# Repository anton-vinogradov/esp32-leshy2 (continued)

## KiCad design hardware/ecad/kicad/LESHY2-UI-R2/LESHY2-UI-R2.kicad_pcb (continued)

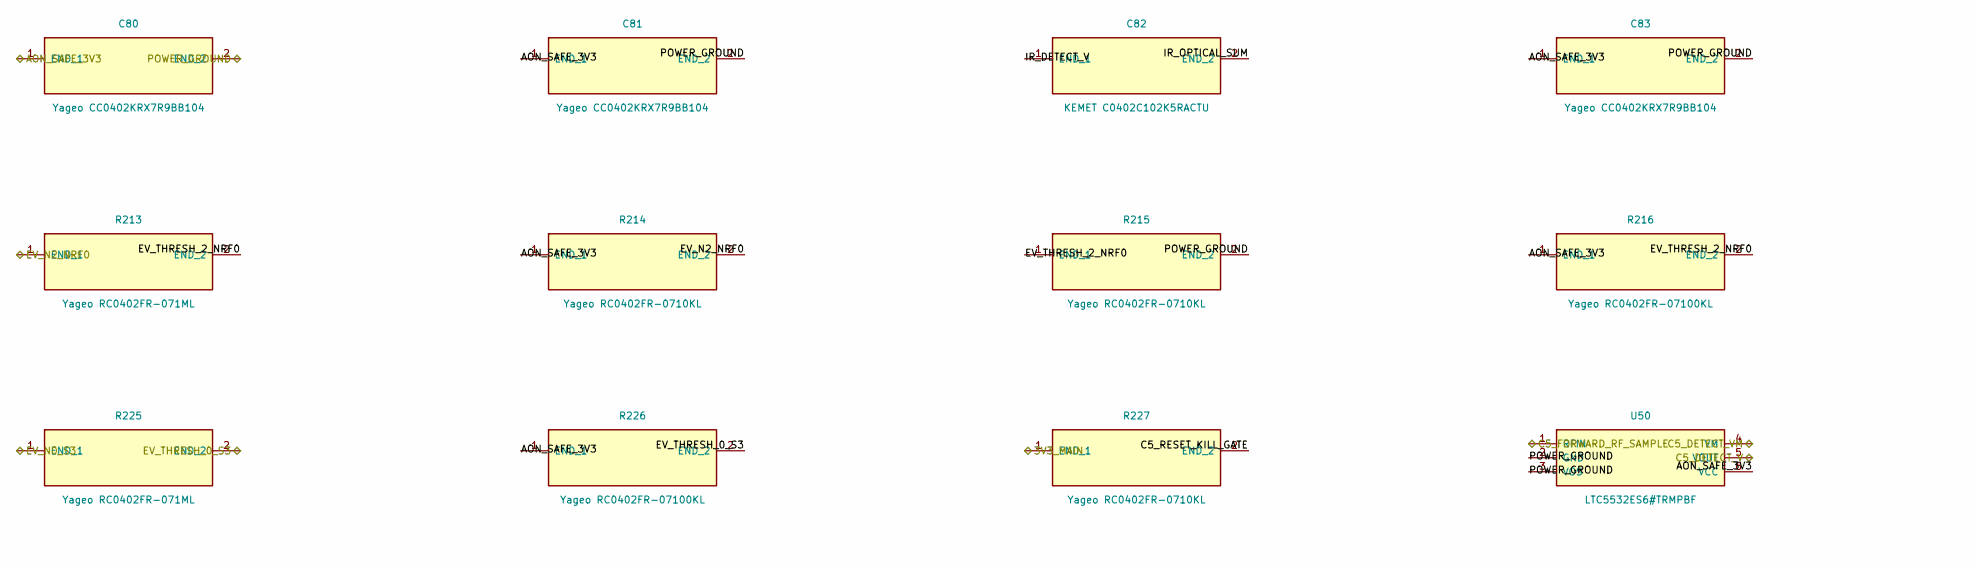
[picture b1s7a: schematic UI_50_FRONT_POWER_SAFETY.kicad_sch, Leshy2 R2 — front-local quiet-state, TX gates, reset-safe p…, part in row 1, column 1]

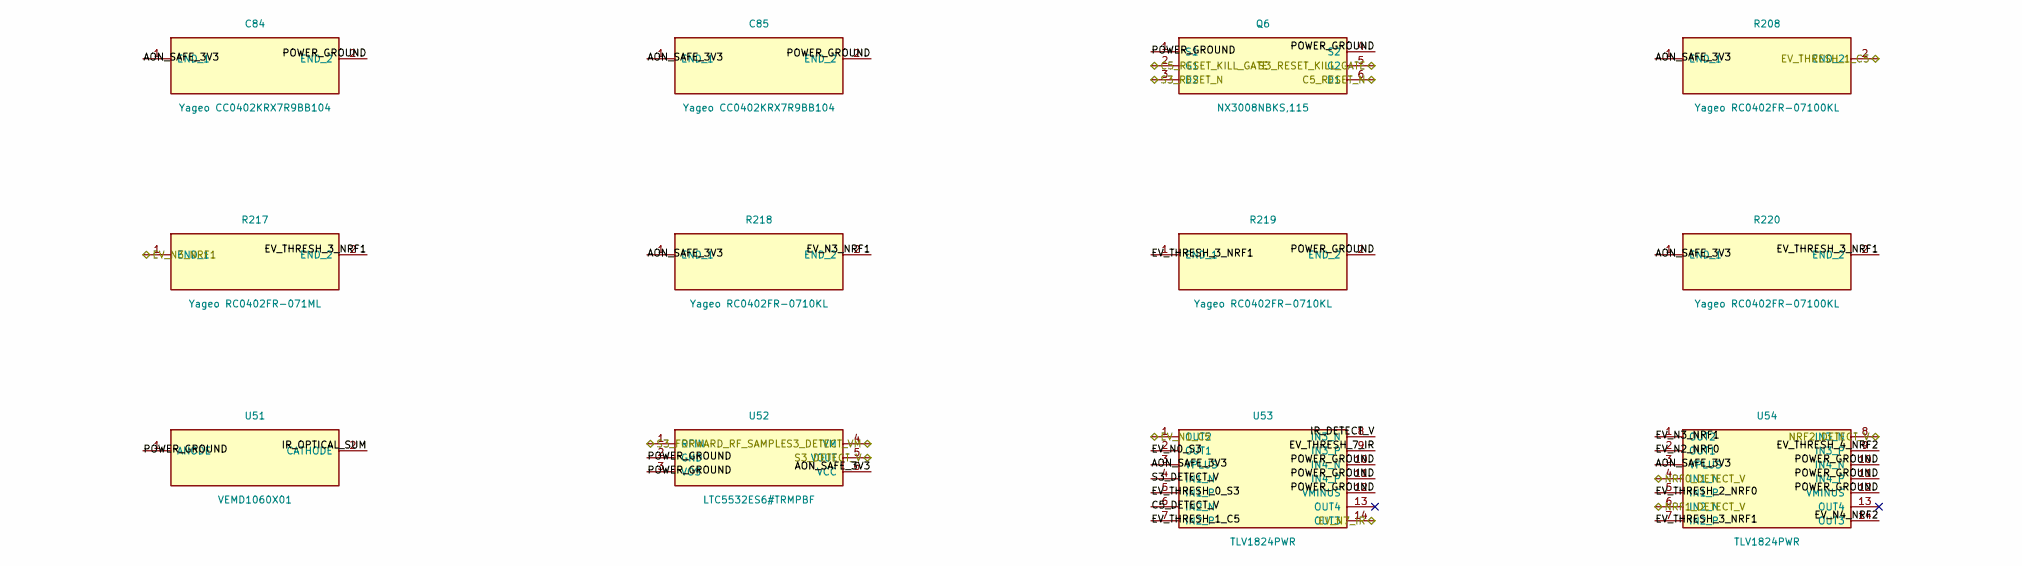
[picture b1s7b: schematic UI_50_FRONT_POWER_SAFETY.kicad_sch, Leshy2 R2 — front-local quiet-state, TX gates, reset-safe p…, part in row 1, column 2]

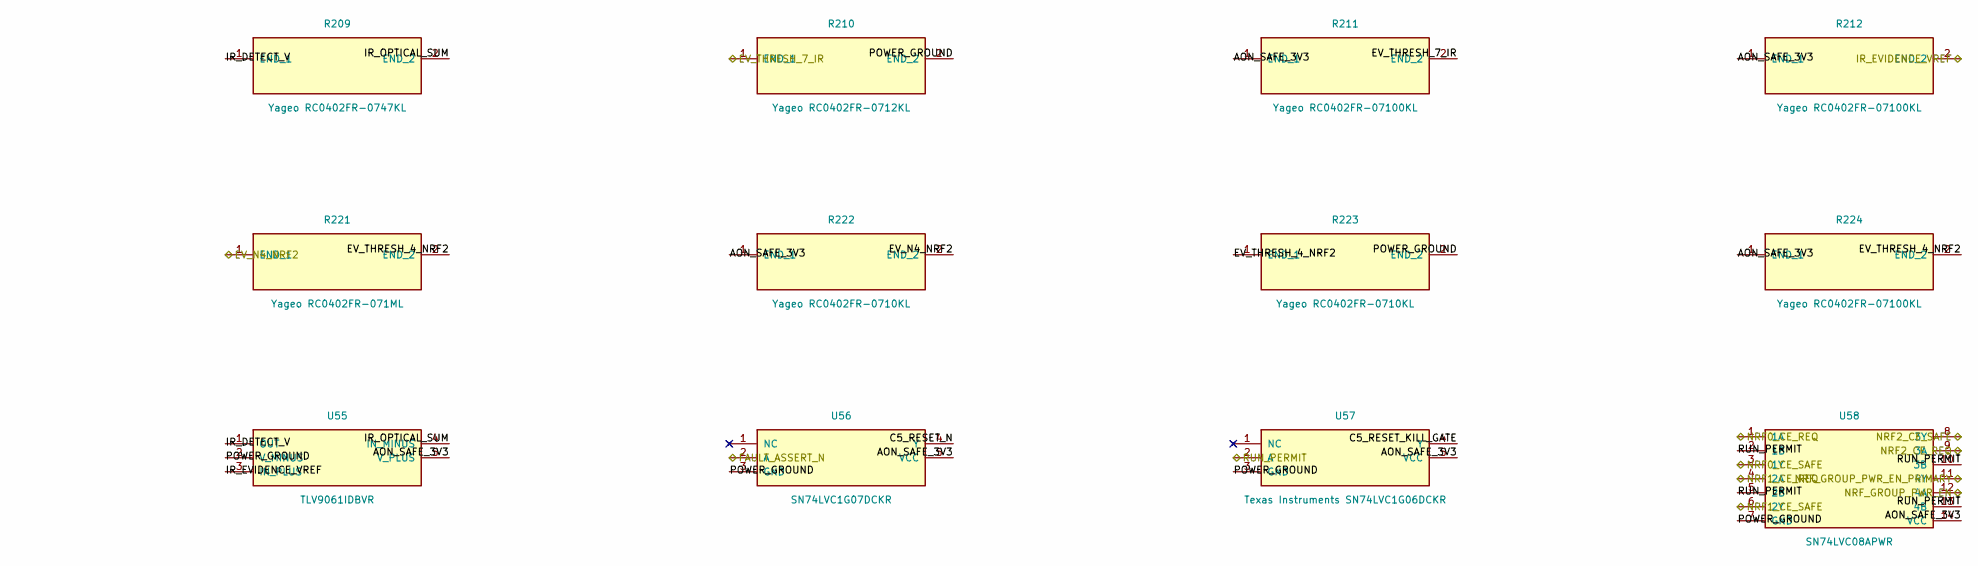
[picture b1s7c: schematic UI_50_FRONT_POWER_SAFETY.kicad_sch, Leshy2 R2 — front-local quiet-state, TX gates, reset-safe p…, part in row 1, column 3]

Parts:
C80, C81, C83, C84, C85: Yageo CC0402KRX7R9BB104; C_0402_1005Metric
C82: KEMET C0402C102K5RACTU; C_0402_1005Metric
Q6: NX3008NBKS,115; SOT-363_SC-70-6
R208, R211, R212, R216, R220, R224, R226: Yageo RC0402FR-07100KL; R_0402_1005Metric
R209: Yageo RC0402FR-0747KL; R_0402_1005Metric
R210: Yageo RC0402FR-0712KL; R_0402_1005Metric
R213, R217, R221, R225: Yageo RC0402FR-071ML; R_0402_1005Metric
R214, R215, R218, R219, R222, R223, R227: Yageo RC0402FR-0710KL; R_0402_1005Metric
U50, U52: LTC5532ES6#TRMPBF; TSOT-23-6
U51: VEMD1060X01
U53, U54: TLV1824PWR; TSSOP-14_4.4x5mm_P0.65mm
U55: TLV9061IDBVR; SOT-23-5
U56: SN74LVC1G07DCKR; Texas_R-PDSO-G5_DCK-5
U57: Texas Instruments SN74LVC1G06DCKR; Texas_R-PDSO-G5_DCK-5
U58: SN74LVC08APWR; TSSOP-14_4.4x5mm_P0.65mm

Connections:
/UI_10_S3_DISPLAY_TOUCH/3V3_MAIN: R227.1 (END_1); also elsewhere on the board
/UI_10_S3_DISPLAY_TOUCH/AON_SAFE_3V3: C80.1 (END_1), C81.1 (END_1), C83.1 (END_1), C84.1 (END_1), C85.1 (END_1), R208.1 (END_1), R211.1 (END_1), R212.1 (END_1), R214.1 (END_1), R216.1 (END_1), R218.1 (END_1), R220.1 (END_1), R222.1 (END_1), R224.1 (END_1), R226.1 (END_1), U50.6 (VCC), U52.6 (VCC), U53.3 (VPLUS), U54.3 (VPLUS), U55.5 (V_PLUS), U56.5 (VCC), U57.5 (VCC), U58.14 (VCC); also elsewhere on the board
/UI_10_S3_DISPLAY_TOUCH/POWER_GROUND: C80.2 (END_2), C81.2 (END_2), C83.2 (END_2), C84.2 (END_2), C85.2 (END_2), Q6.1 (S1), Q6.4 (S2), R210.2 (END_2), R215.2 (END_2), R219.2 (END_2), R223.2 (END_2), U50.2 (GND), U50.3 (VOS), U51.1 (ANODE), U52.2 (GND), U52.3 (VOS), U53.10 (IN4_N), U53.11 (IN4_P), U53.12 (VMINUS), U54.10 (IN4_N), U54.11 (IN4_P), U54.12 (VMINUS), U55.2 (V_MINUS), U56.3 (GND), U57.3 (GND), U58.7 (GND); also elsewhere on the board
/UI_10_S3_DISPLAY_TOUCH/S3_DETECT_V: U52.5 (VOUT), U53.4 (IN1_N); also elsewhere on the board
/UI_10_S3_DISPLAY_TOUCH/S3_DETECT_VM: U52.4 (VM); also elsewhere on the board
/UI_10_S3_DISPLAY_TOUCH/S3_FORWARD_RF_SAMPLE: U52.1 (RFIN); also elsewhere on the board
/UI_10_S3_DISPLAY_TOUCH/S3_RESET_KILL_GATE: Q6.5 (G2); also elsewhere on the board
/UI_10_S3_DISPLAY_TOUCH/S3_RESET_N: Q6.3 (D2); also elsewhere on the board
/UI_20_C5_WIFI_IR_SERVICE/C5_DETECT_V: U50.5 (VOUT), U53.6 (IN2_N); also elsewhere on the board
/UI_20_C5_WIFI_IR_SERVICE/C5_DETECT_VM: U50.4 (VM); also elsewhere on the board
/UI_20_C5_WIFI_IR_SERVICE/C5_FORWARD_RF_SAMPLE: U50.1 (RFIN); also elsewhere on the board
/UI_20_C5_WIFI_IR_SERVICE/C5_RESET_N: Q6.6 (D1), U56.4 (Y); also elsewhere on the board
/UI_20_C5_WIFI_IR_SERVICE/EV_N1_C5: U53.1 (OUT2); also elsewhere on the board
/UI_20_C5_WIFI_IR_SERVICE/EV_N7_IR: U53.14 (OUT3); also elsewhere on the board
/UI_20_C5_WIFI_IR_SERVICE/EV_THRESH_1_C5: R208.2 (END_2), U53.7 (IN2_P); also elsewhere on the board
/UI_20_C5_WIFI_IR_SERVICE/FAULT_ASSERT_N: U56.2 (A); also elsewhere on the board
/UI_20_C5_WIFI_IR_SERVICE/IR_EVIDENCE_VREF: R212.2 (END_2), U55.3 (IN_PLUS); also elsewhere on the board
/UI_20_C5_WIFI_IR_SERVICE/RUN_PERMIT: U57.2 (A), U58.2 (1B), U58.5 (2B), U58.10 (3B), U58.13 (4B); also elsewhere on the board
/UI_30_HUB_RP_CORE_SERVICE/NRF0_CE_REQ: U58.1 (1A); also elsewhere on the board
/UI_30_HUB_RP_CORE_SERVICE/NRF1_CE_REQ: U58.4 (2A); also elsewhere on the board
/UI_30_HUB_RP_CORE_SERVICE/NRF2_CE_REQ: U58.9 (3A); also elsewhere on the board
/UI_30_HUB_RP_CORE_SERVICE/NRF_GROUP_PWR_EN: U58.12 (4A); also elsewhere on the board
/UI_31_NRF24_X3_TX_EVIDENCE/NRF0_CE_SAFE: U58.3 (1Y); also elsewhere on the board
/UI_31_NRF24_X3_TX_EVIDENCE/NRF0_DETECT_V: U54.4 (IN1_N); also elsewhere on the board
/UI_31_NRF24_X3_TX_EVIDENCE/NRF1_CE_SAFE: U58.6 (2Y); also elsewhere on the board
/UI_31_NRF24_X3_TX_EVIDENCE/NRF1_DETECT_V: U54.6 (IN2_N); also elsewhere on the board
/UI_31_NRF24_X3_TX_EVIDENCE/NRF2_CE_SAFE: U58.8 (3Y); also elsewhere on the board
/UI_31_NRF24_X3_TX_EVIDENCE/NRF2_DETECT_V: U54.8 (IN3_N); also elsewhere on the board
/UI_31_NRF24_X3_TX_EVIDENCE/NRF_GROUP_PWR_EN_PRIMARY: U58.11 (4Y); also elsewhere on the board
/UI_50_FRONT_POWER_SAFETY/C5_RESET_KILL_GATE: Q6.2 (G1), R227.2 (END_2), U57.4 (Y); also elsewhere on the board
/UI_50_FRONT_POWER_SAFETY/EV_N0_S3: R225.1 (END_1), U53.2 (OUT1); also elsewhere on the board
/UI_50_FRONT_POWER_SAFETY/EV_N2_NRF0: R213.1 (END_1), R214.2 (END_2), U54.2 (OUT1); also elsewhere on the board
/UI_50_FRONT_POWER_SAFETY/EV_N3_NRF1: R217.1 (END_1), R218.2 (END_2), U54.1 (OUT2); also elsewhere on the board
/UI_50_FRONT_POWER_SAFETY/EV_N4_NRF2: R221.1 (END_1), R222.2 (END_2), U54.14 (OUT3); also elsewhere on the board
/UI_50_FRONT_POWER_SAFETY/EV_THRESH_0_S3: R225.2 (END_2), R226.2 (END_2), U53.5 (IN1_P); also elsewhere on the board
/UI_50_FRONT_POWER_SAFETY/EV_THRESH_2_NRF0: R213.2 (END_2), R215.1 (END_1), R216.2 (END_2), U54.5 (IN1_P)
/UI_50_FRONT_POWER_SAFETY/EV_THRESH_3_NRF1: R217.2 (END_2), R219.1 (END_1), R220.2 (END_2), U54.7 (IN2_P)
/UI_50_FRONT_POWER_SAFETY/EV_THRESH_4_NRF2: R221.2 (END_2), R223.1 (END_1), R224.2 (END_2), U54.9 (IN3_P)
/UI_50_FRONT_POWER_SAFETY/EV_THRESH_7_IR: R210.1 (END_1), R211.2 (END_2), U53.9 (IN3_P); also elsewhere on the board
/UI_50_FRONT_POWER_SAFETY/IR_DETECT_V: C82.1 (END_1), R209.1 (END_1), U53.8 (IN3_N), U55.1 (OUT)
/UI_50_FRONT_POWER_SAFETY/IR_OPTICAL_SUM: C82.2 (END_2), R209.2 (END_2), U51.2 (CATHODE), U55.4 (IN_MINUS)

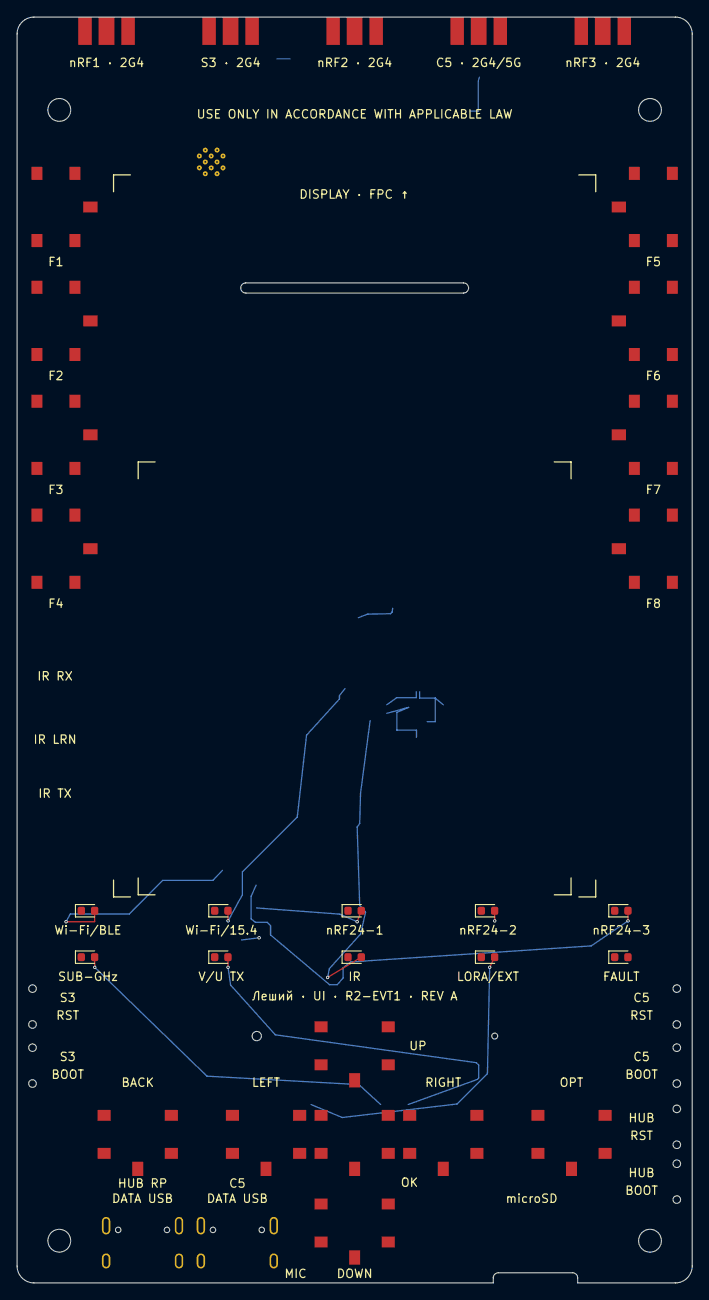
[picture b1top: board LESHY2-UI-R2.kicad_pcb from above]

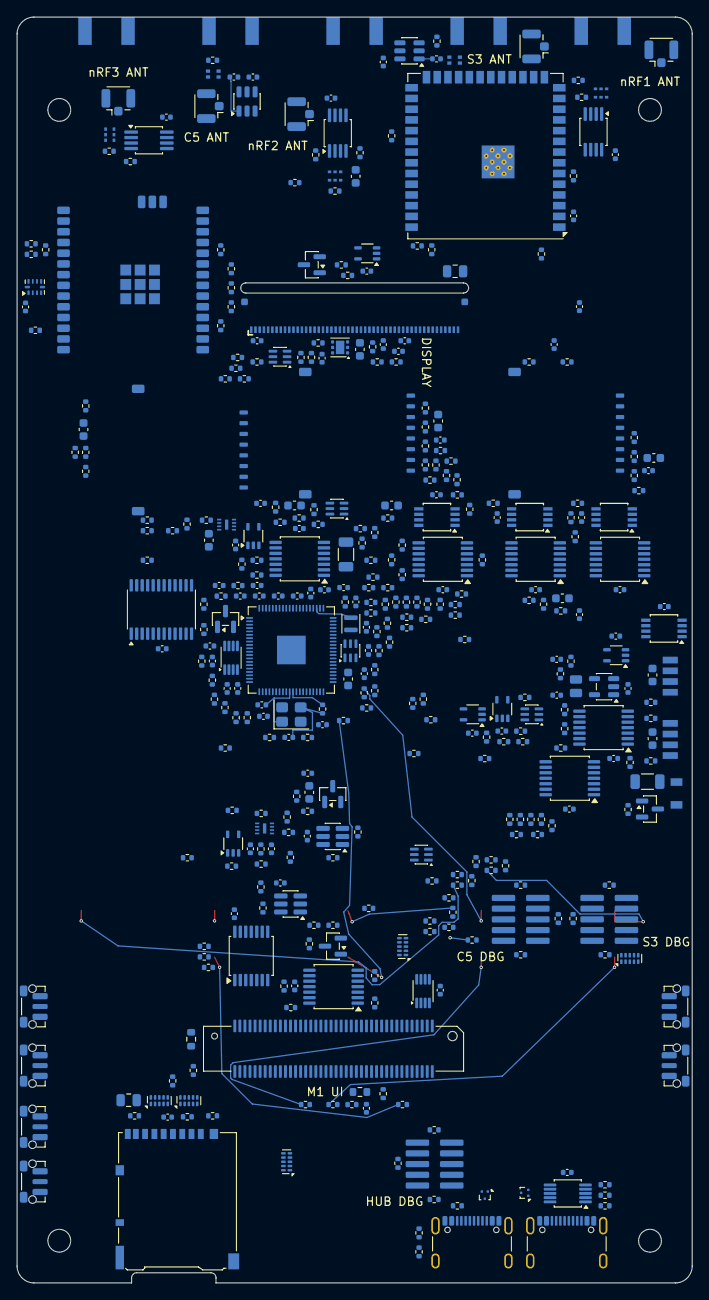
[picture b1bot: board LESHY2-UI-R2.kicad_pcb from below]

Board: 6 copper layers, 80.0 x 150.0 mm, 434 parts (400 on the bottom side), 307 nets.

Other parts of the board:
MH1, MH2, MH3, MH4: M2.5 compression-stop axis; MountingHole_2.7mm_M2.5

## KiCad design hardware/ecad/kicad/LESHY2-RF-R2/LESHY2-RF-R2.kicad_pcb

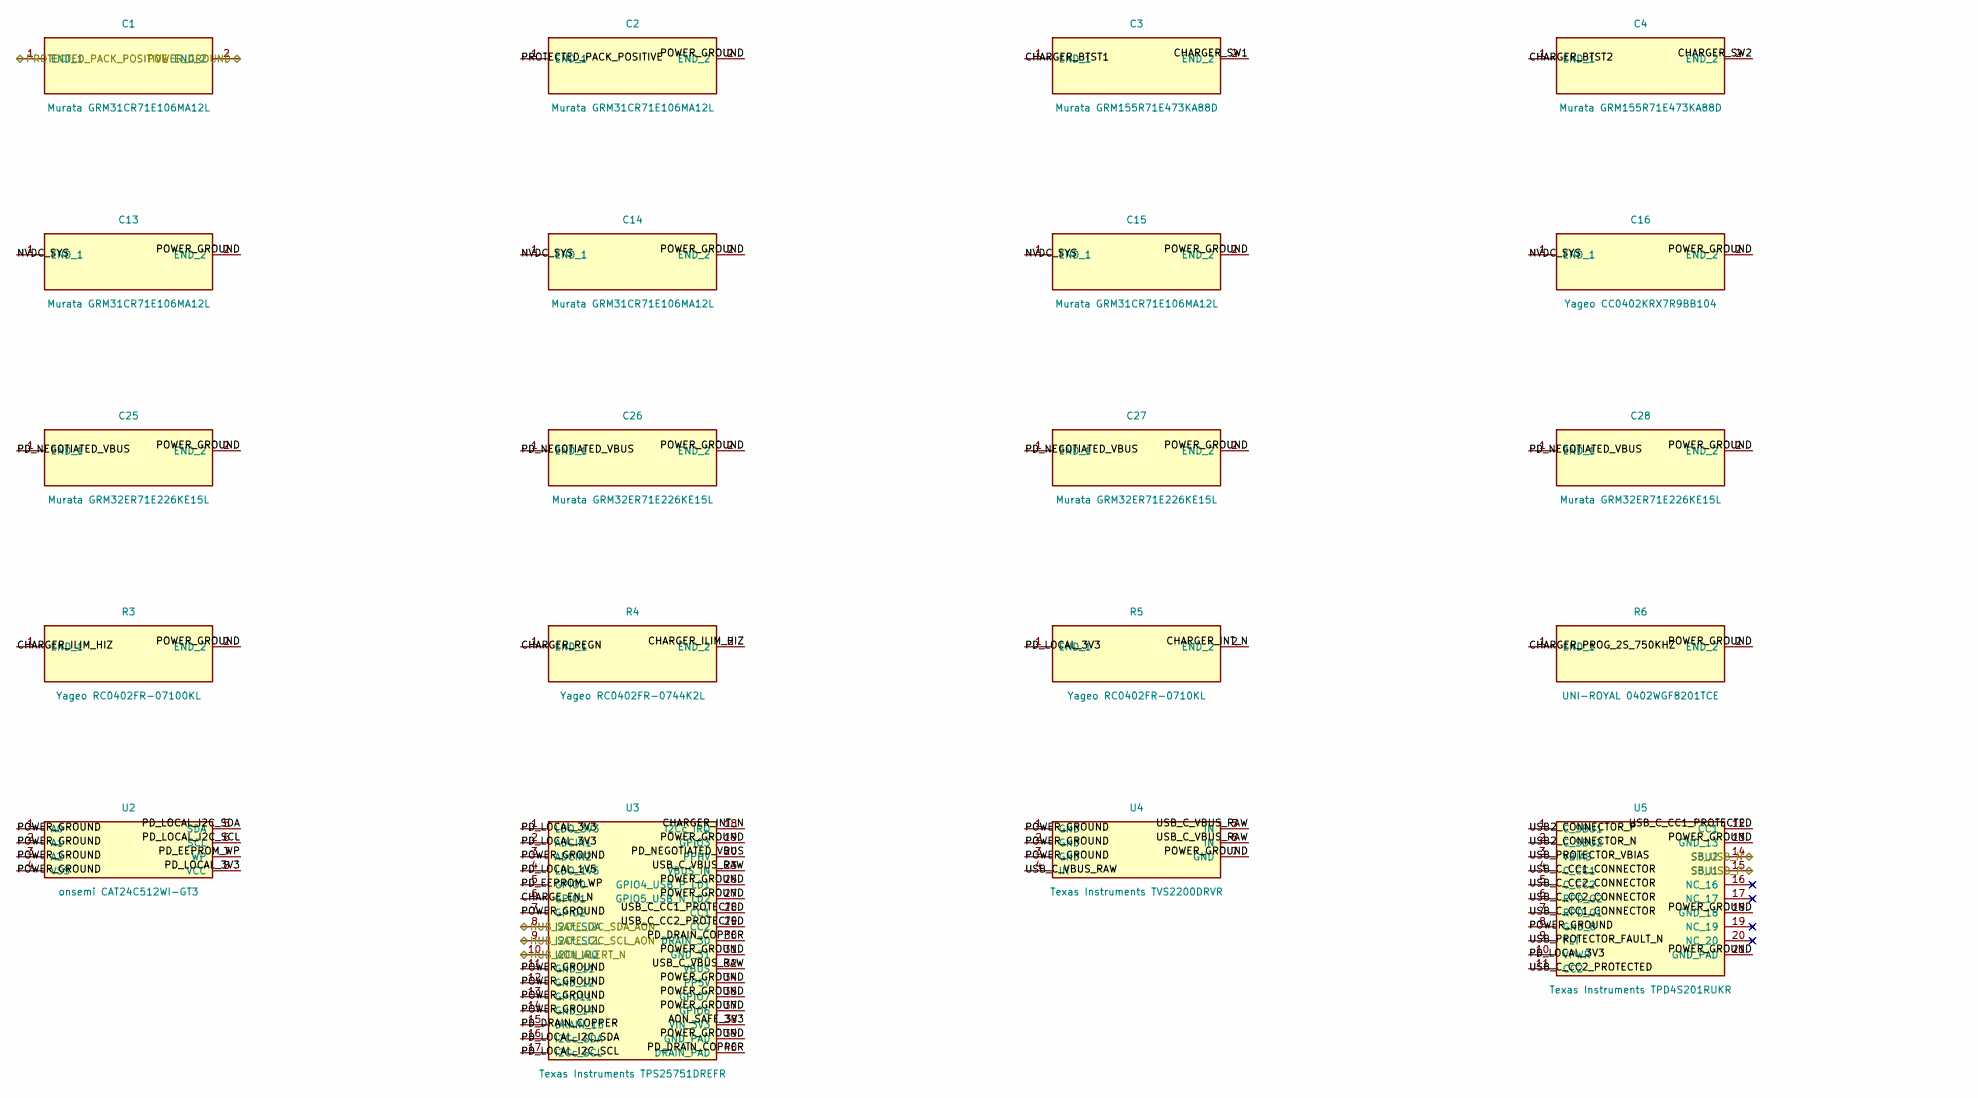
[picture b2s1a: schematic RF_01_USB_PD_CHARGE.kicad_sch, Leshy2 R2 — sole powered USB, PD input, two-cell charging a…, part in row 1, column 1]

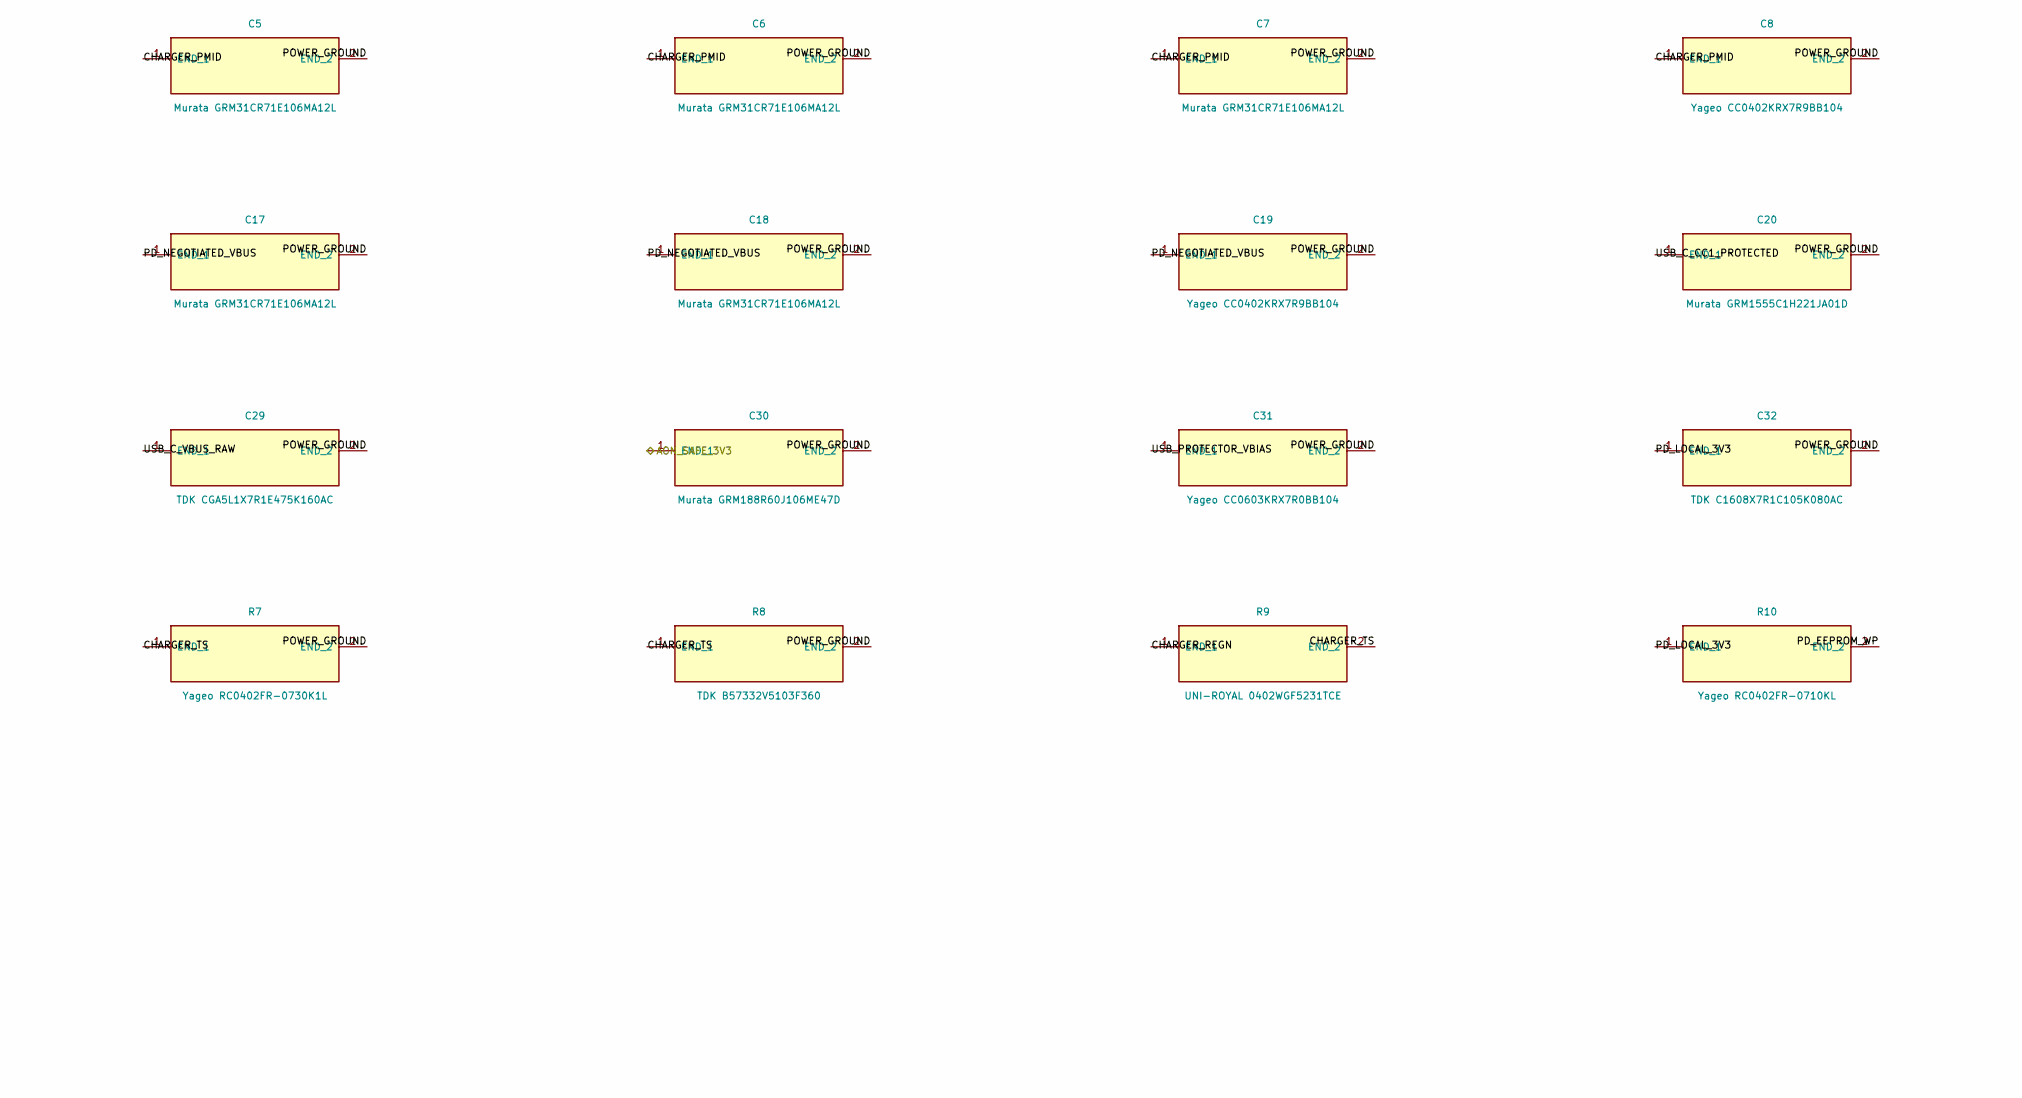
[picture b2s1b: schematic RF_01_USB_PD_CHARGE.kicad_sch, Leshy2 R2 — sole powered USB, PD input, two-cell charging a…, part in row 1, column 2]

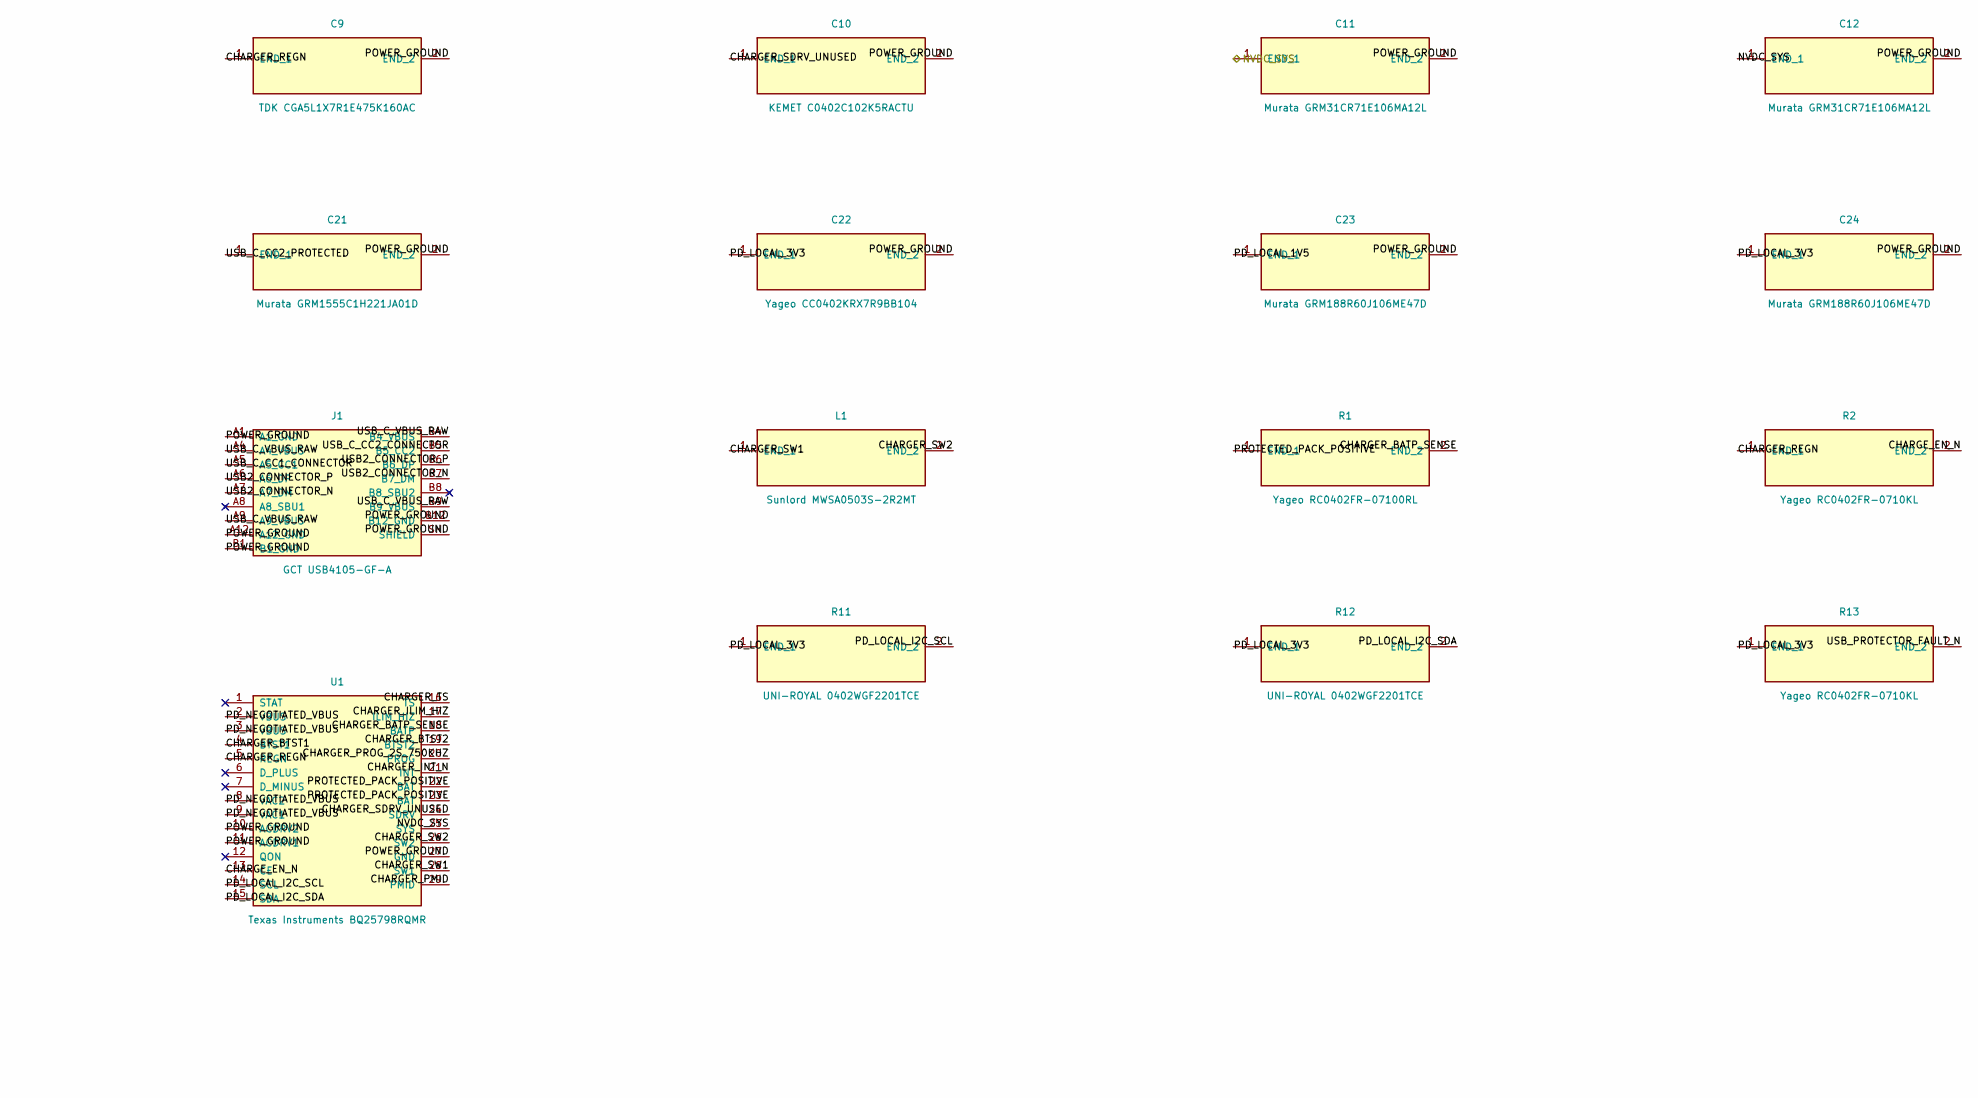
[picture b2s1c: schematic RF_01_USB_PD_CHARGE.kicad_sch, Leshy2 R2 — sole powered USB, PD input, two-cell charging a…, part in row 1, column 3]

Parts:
C1, C2, C5, C6, C7, C11, C12, C13, C14, C15, C17, C18: Murata GRM31CR71E106MA12L; C_1206_3216Metric
C3, C4: Murata GRM155R71E473KA88D; C_0402_1005Metric
C8, C16, C19, C22: Yageo CC0402KRX7R9BB104; C_0402_1005Metric
C9, C29: TDK CGA5L1X7R1E475K160AC; C_1206_3216Metric
C10: KEMET C0402C102K5RACTU; C_0402_1005Metric
C20, C21: Murata GRM1555C1H221JA01D; C_0402_1005Metric
C23, C24, C30: Murata GRM188R60J106ME47D; C_0603_1608Metric
C25, C26, C27, C28: Murata GRM32ER71E226KE15L; C_1210_3225Metric
C31: Yageo CC0603KRX7R0BB104; C_0603_1608Metric
C32: TDK C1608X7R1C105K080AC; C_0603_1608Metric
J1: GCT USB4105-GF-A; USB_C_Receptacle_GCT_USB4105-xx-A_16P_TopMnt_Horizontal
L1: Sunlord MWSA0503S-2R2MT; L_Sunlord_MWSA0503S
R1: Yageo RC0402FR-07100RL; R_0402_1005Metric
R2, R5, R10, R13: Yageo RC0402FR-0710KL; R_0402_1005Metric
R3: Yageo RC0402FR-07100KL; R_0402_1005Metric
R4: Yageo RC0402FR-0744K2L; R_0402_1005Metric
R6: UNI-ROYAL 0402WGF8201TCE; R_0402_1005Metric
R7: Yageo RC0402FR-0730K1L; R_0402_1005Metric
R8: TDK B57332V5103F360; R_0603_1608Metric
R9: UNI-ROYAL 0402WGF5231TCE; R_0402_1005Metric
R11, R12: UNI-ROYAL 0402WGF2201TCE; R_0402_1005Metric
U1: Texas Instruments BQ25798RQMR; Texas_RQM0029A_VQFN-29_4x4mm_P0.4mm
U2: onsemi CAT24C512WI-GT3; SOIC-8_3.9x4.9mm_P1.27mm
U3: Texas Instruments TPS25751DREFR; Texas_REF0038A_WQFN-38-2EP_6x4mm_P0.4
U4: Texas Instruments TVS2200DRVR; WSON-6-1EP_2x2mm_P0.65mm_EP1x1.6mm
U5: Texas Instruments TPD4S201RUKR; Texas_RUK0020B_WQFN-20-1EP_3x3mm_P0.4mm_EP1.7x1.7mm

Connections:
/RF_01_USB_PD_CHARGE/AON_SAFE_3V3: C30.1 (END_1), U3.38 (VIN_3V3); also elsewhere on the board
/RF_01_USB_PD_CHARGE/CHARGER_BATP_SENSE: R1.2 (END_2), U1.18 (BATP)
/RF_01_USB_PD_CHARGE/CHARGER_BTST1: C3.1 (END_1), U1.4 (BTST1)
/RF_01_USB_PD_CHARGE/CHARGER_BTST2: C4.1 (END_1), U1.19 (BTST2)
/RF_01_USB_PD_CHARGE/CHARGER_ILIM_HIZ: R3.1 (END_1), R4.2 (END_2), U1.17 (ILIM_HIZ)
/RF_01_USB_PD_CHARGE/CHARGER_INT_N: R5.2 (END_2), U1.21 (INT), U3.18 (I2Cc_IRQ)
/RF_01_USB_PD_CHARGE/CHARGER_PMID: C5.1 (END_1), C6.1 (END_1), C7.1 (END_1), C8.1 (END_1), U1.29 (PMID)
/RF_01_USB_PD_CHARGE/CHARGER_PROG_2S_750KHZ: R6.1 (END_1), U1.20 (PROG)
/RF_01_USB_PD_CHARGE/CHARGER_REGN: C9.1 (END_1), R2.1 (END_1), R4.1 (END_1), R9.1 (END_1), U1.5 (REGN)
/RF_01_USB_PD_CHARGE/CHARGER_SDRV_UNUSED: C10.1 (END_1), U1.24 (SDRV)
/RF_01_USB_PD_CHARGE/CHARGER_SW1: C3.2 (END_2), L1.1 (END_1), U1.28 (SW1)
/RF_01_USB_PD_CHARGE/CHARGER_SW2: C4.2 (END_2), L1.2 (END_2), U1.26 (SW2)
/RF_01_USB_PD_CHARGE/CHARGER_TS: R7.1 (END_1), R8.1 (END_1), R9.2 (END_2), U1.16 (TS)
/RF_01_USB_PD_CHARGE/CHARGE_EN_N: R2.2 (END_2), U1.13 (CE), U3.6 (GPIO1)
/RF_01_USB_PD_CHARGE/NVDC_SYS: C11.1 (END_1), C12.1 (END_1), C13.1 (END_1), C14.1 (END_1), C15.1 (END_1), C16.1 (END_1), U1.25 (SYS); also elsewhere on the board
/RF_01_USB_PD_CHARGE/PD_DRAIN_COPPER: U3.15 (DRAIN_15), U3.30 (DRAIN_30), U3.40 (DRAIN_PAD)
/RF_01_USB_PD_CHARGE/PD_EEPROM_WP: R10.2 (END_2), U2.7 (WP), U3.5 (GPIO0)
/RF_01_USB_PD_CHARGE/PD_LOCAL_1V5: C23.1 (END_1), U3.4 (LDO_1V5)
/RF_01_USB_PD_CHARGE/PD_LOCAL_3V3: C22.1 (END_1), C24.1 (END_1), C32.1 (END_1), R5.1 (END_1), R10.1 (END_1), R11.1 (END_1), R12.1 (END_1), R13.1 (END_1), U2.8 (VCC), U3.1 (LDO_3V3), U3.2 (ADCIN1), U5.10 (VPWR)
/RF_01_USB_PD_CHARGE/PD_LOCAL_I2C_SCL: R11.2 (END_2), U1.14 (SCL), U2.6 (SCL), U3.17 (I2Cc_SCL)
/RF_01_USB_PD_CHARGE/PD_LOCAL_I2C_SDA: R12.2 (END_2), U1.15 (SDA), U2.5 (SDA), U3.16 (I2Cc_SDA)
/RF_01_USB_PD_CHARGE/PD_NEGOTIATED_VBUS: C17.1 (END_1), C18.1 (END_1), C19.1 (END_1), C25.1 (END_1), C26.1 (END_1), C27.1 (END_1), C28.1 (END_1), U1.2 (VBUS), U1.3 (VBUS), U1.8 (VAC2), U1.9 (VAC1), U3.20 (PPHV)
/RF_01_USB_PD_CHARGE/POWER_GROUND: C1.2 (END_2), C2.2 (END_2), C5.2 (END_2), C6.2 (END_2), C7.2 (END_2), C8.2 (END_2), C9.2 (END_2), C10.2 (END_2), C11.2 (END_2), C12.2 (END_2), C13.2 (END_2), C14.2 (END_2), C15.2 (END_2), C16.2 (END_2), C17.2 (END_2), C18.2 (END_2), C19.2 (END_2), C20.2 (END_2), C21.2 (END_2), C22.2 (END_2), C23.2 (END_2), C24.2 (END_2), C25.2 (END_2), C26.2 (END_2), C27.2 (END_2), C28.2 (END_2), C29.2 (END_2), C30.2 (END_2), C31.2 (END_2), C32.2 (END_2), J1.A1 (A1_GND), J1.A12 (A12_GND), J1.B1 (B1_GND), J1.B12 (B12_GND), J1.SH (SHIELD), R3.2 (END_2), R6.2 (END_2), R7.2 (END_2), R8.2 (END_2), U1.10 (ACDRV2), U1.11 (ACDRV1), U1.27 (GND), U2.1 (A0), U2.2 (A1), U2.3 (A2), U2.4 (VSS), U3.3 (ADCIN2), U3.7 (GPIO2), U3.11 (GND_11), U3.12 (GND_12), U3.13 (GPIO11), U3.14 (GND_14), U3.19 (GPIO3), U3.26 (GPIO4_USB_P_LD1), U3.27 (GPIO5_USB_N_LD2), U3.31 (GND_31), U3.34 (PP5V), U3.36 (GPIO7), U3.37 (GPIO6), U3.39 (GND_PAD), U4.1 (GND), U4.2 (GND), U4.3 (GND), U4.7 (GND), U5.8 (GND_8), U5.13 (GND_13), U5.18 (GND_18), U5.21 (GND_PAD); also elsewhere on the board
/RF_01_USB_PD_CHARGE/PROTECTED_PACK_POSITIVE: C1.1 (END_1), C2.1 (END_1), R1.1 (END_1), U1.22 (BAT), U1.23 (BAT); also elsewhere on the board
/RF_01_USB_PD_CHARGE/S3_USB_N: U5.14 (SBU2); also elsewhere on the board
/RF_01_USB_PD_CHARGE/S3_USB_P: U5.15 (SBU1); also elsewhere on the board
/RF_01_USB_PD_CHARGE/USB2_CONNECTOR_N: J1.A7 (A7_DM), J1.B7 (B7_DM), U5.2 (C_SBU2)
/RF_01_USB_PD_CHARGE/USB2_CONNECTOR_P: J1.A6 (A6_DP), J1.B6 (B6_DP), U5.1 (C_SBU1)
/RF_01_USB_PD_CHARGE/USB_C_CC1_CONNECTOR: J1.A5 (A5_CC1), U5.4 (C_CC1), U5.7 (RPD_G1)
/RF_01_USB_PD_CHARGE/USB_C_CC1_PROTECTED: C20.1 (END_1), U3.28 (CC1), U5.12 (CC1)
/RF_01_USB_PD_CHARGE/USB_C_CC2_CONNECTOR: J1.B5 (B5_CC2), U5.5 (C_CC2), U5.6 (RPD_G2)
/RF_01_USB_PD_CHARGE/USB_C_CC2_PROTECTED: C21.1 (END_1), U3.29 (CC2), U5.11 (CC2)
/RF_01_USB_PD_CHARGE/USB_C_VBUS_RAW: C29.1 (END_1), J1.A4 (A4_VBUS), J1.A9 (A9_VBUS), J1.B4 (B4_VBUS), J1.B9 (B9_VBUS), U3.23 (VBUS_IN), U3.32 (VBUS), U4.4 (IN), U4.5 (IN), U4.6 (IN)
/RF_01_USB_PD_CHARGE/USB_PROTECTOR_FAULT_N: R13.2 (END_2), U5.9 (FLT)
/RF_01_USB_PD_CHARGE/USB_PROTECTOR_VBIAS: C31.1 (END_1), U5.3 (VBIAS)
/RF_02_PACK_SAFETY_AON/HUB_SAFE_I2C_SCL_AON: U3.9 (I2Ct_SCL); also elsewhere on the board
/RF_02_PACK_SAFETY_AON/HUB_SAFE_I2C_SDA_AON: U3.8 (I2Ct_SDA); also elsewhere on the board
/RF_50_TX_SAFETY_EVIDENCE/HUB_AON_ALERT_N: U3.10 (I2Ct_IRQ); also elsewhere on the board
